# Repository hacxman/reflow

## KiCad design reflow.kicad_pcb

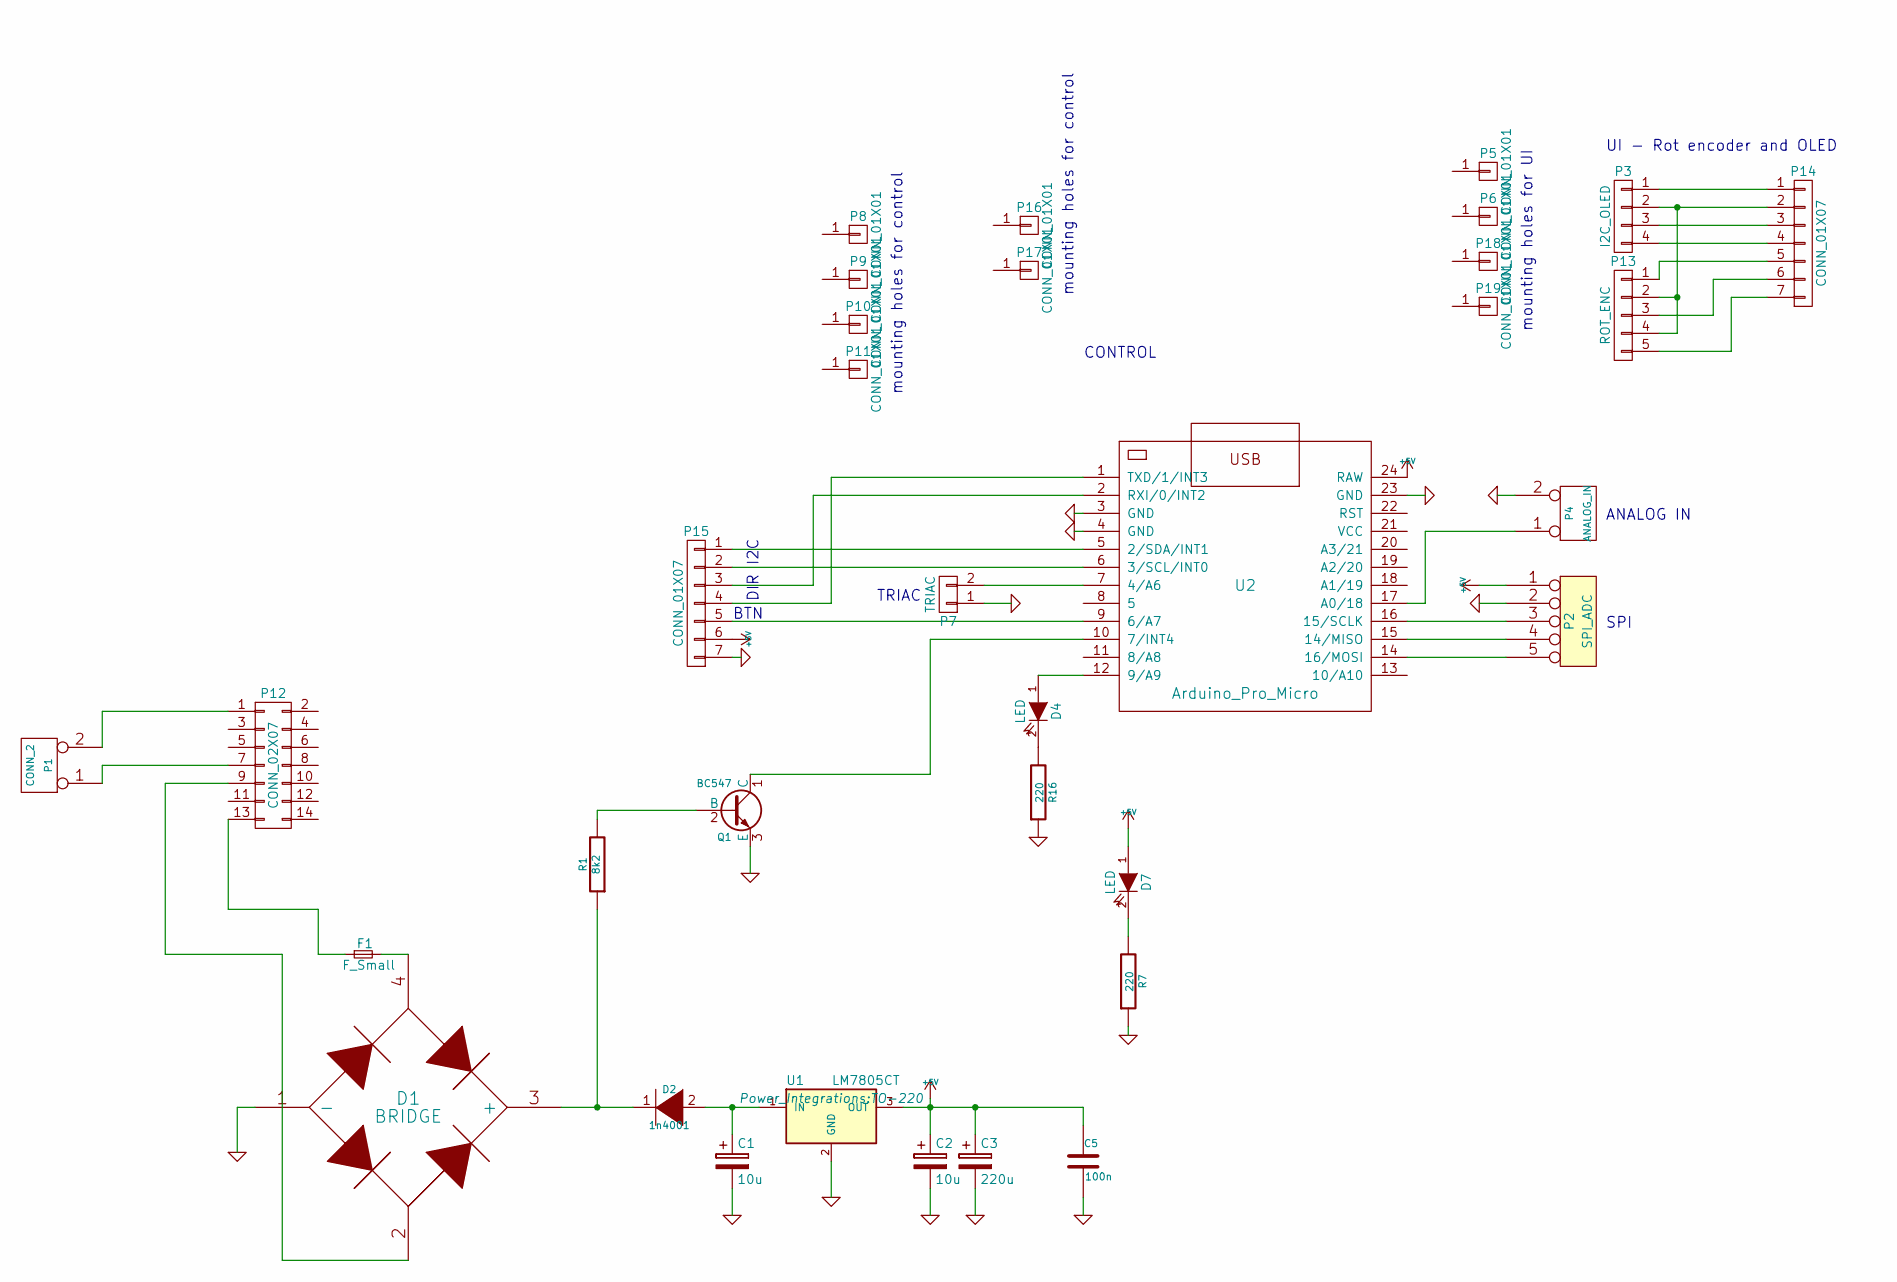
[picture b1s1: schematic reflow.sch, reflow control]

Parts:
C1, C2: 10u; C_Radial_D6.3_L11.2_P2.5
C3: 220u; C_Radial_D6.3_L11.2_P2.5
C5: 100n; C_Rect_L7_W2.5_P5
D1: BRIDGE; SDB107
D2: 1n4001; Diode_DO-35_SOD27_Horizontal_RM10
D4, D7: LED; LED-5MM
F1: F_Small; Fuseholder5x20_horiz_SemiClosed_Casing10x25mm
P1: CONN_2; TerminalBlock_Pheonix_MPT-2.54mm_2pol
P2: SPI_ADC; Pin_Header_Straight_1x05
P3: I2C_OLED; Pin_Header_Straight_1x04
P4: ANALOG_IN; Pin_Header_Straight_1x02
P5, P6, P8, P9, P10, P11, P16, P17, P18, P19: CONN_01X01; MountingHole_3mm
P7: TRIAC; Pin_Header_Straight_1x02
P12: CONN_02X07; Trafo_CHK-EI54-16VA_1xSec
P13: ROT_ENC; ROT_ENC_DIP-6_W15.24mm_LongPads
P14, P15: CONN_01X07; Pin_Header_Straight_1x07
Q1: BC547; TO-92_Molded_Wide_Oval
R1: 8k2; Resistor_Horizontal_RM10mm
R7, R16: 220; Resistor_Horizontal_RM10mm
U1: LM7805CT; TO-220
U2: Arduino_Pro_Micro; DIP-24_W15.24mm_LongPads

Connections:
+5V: C2.1, C3.1, C5.1, D7.1 (A), P2.1, P15.6, U1.3 (OUT), U2.24 (RAW)
GND: C1.2, C2.2, C3.2, C5.2, D1.1 (-), P2.2, P4.2 (PM), P7.1, P15.7, Q1.3 (E), R7.1, R16.1, U1.2 (GND), U2.3 (GND), U2.4 (GND), U2.23 (GND)
unnamed: C1.1, D2.2 (A), U1.1 (IN)
unnamed: D1.2, P12.9
unnamed: D1.3 (+), D2.1 (K), R1.1
unnamed: D1.4, F1.2
unnamed: D4.1 (A), U2.12 (9/A9)
unnamed: D4.2 (K), R16.2
unnamed: D7.2 (K), R7.2
unnamed: F1.1, P12.13
unnamed: P1.1, P12.7
unnamed: P1.2 (PM), P12.1
unnamed: P2.3, U2.16 (15/SCLK)
unnamed: P2.4, U2.15 (14/MISO)
unnamed: P2.5, U2.14 (16/MOSI)
unnamed: P4.1, U2.17 (A0/18)
unnamed: P7.2, U2.7 (4/A6)
unnamed: P13.1, P14.5
unnamed: P3.2, P13.2, P13.4, P14.2
unnamed: P13.3, P14.6
unnamed: P13.5, P14.7
unnamed: P3.1, P14.1
unnamed: P3.3, P14.3
unnamed: P3.4, P14.4
unnamed: P15.1, U2.5 (2/SDA/INT1)
unnamed: P15.2, U2.6 (3/SCL/INT0)
unnamed: P15.3, U2.2 (RXI/0/INT2)
unnamed: P15.4, U2.1 (TXD/1/INT3)
unnamed: P15.5, U2.9 (6/A7)
unnamed: Q1.1 (C), U2.10 (7/INT4)
unnamed: Q1.2 (B), R1.2

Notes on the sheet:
ANALOG IN
CONTROL
TRIAC
SPI
mounting holes for control
DIR
BTN
I2C
UI - Rot encoder and OLED
mounting holes for UI

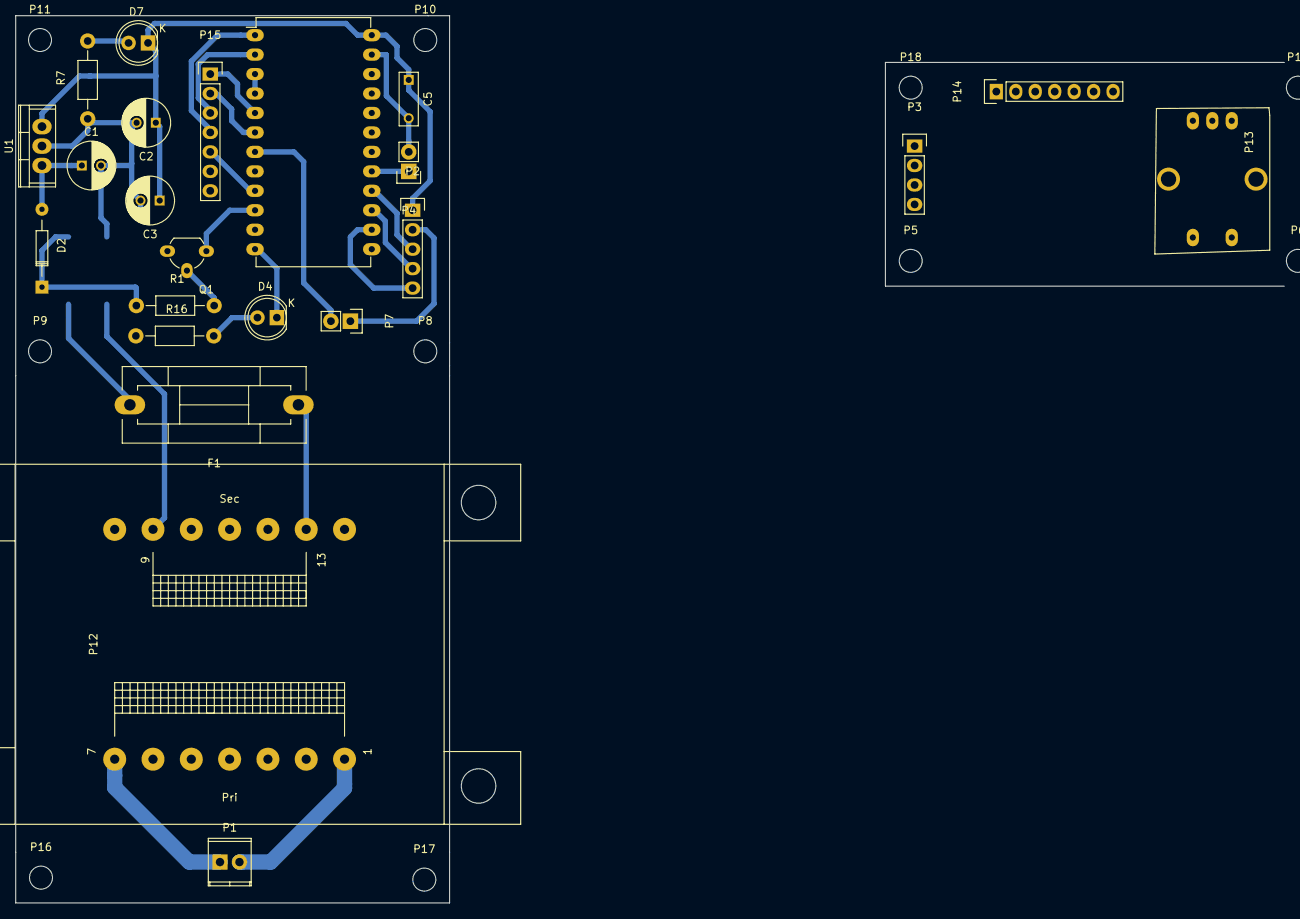
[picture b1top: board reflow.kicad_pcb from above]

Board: 2 copper layers, 165.6 x 115.8 mm, 34 parts (1 on the bottom side), 31 nets.

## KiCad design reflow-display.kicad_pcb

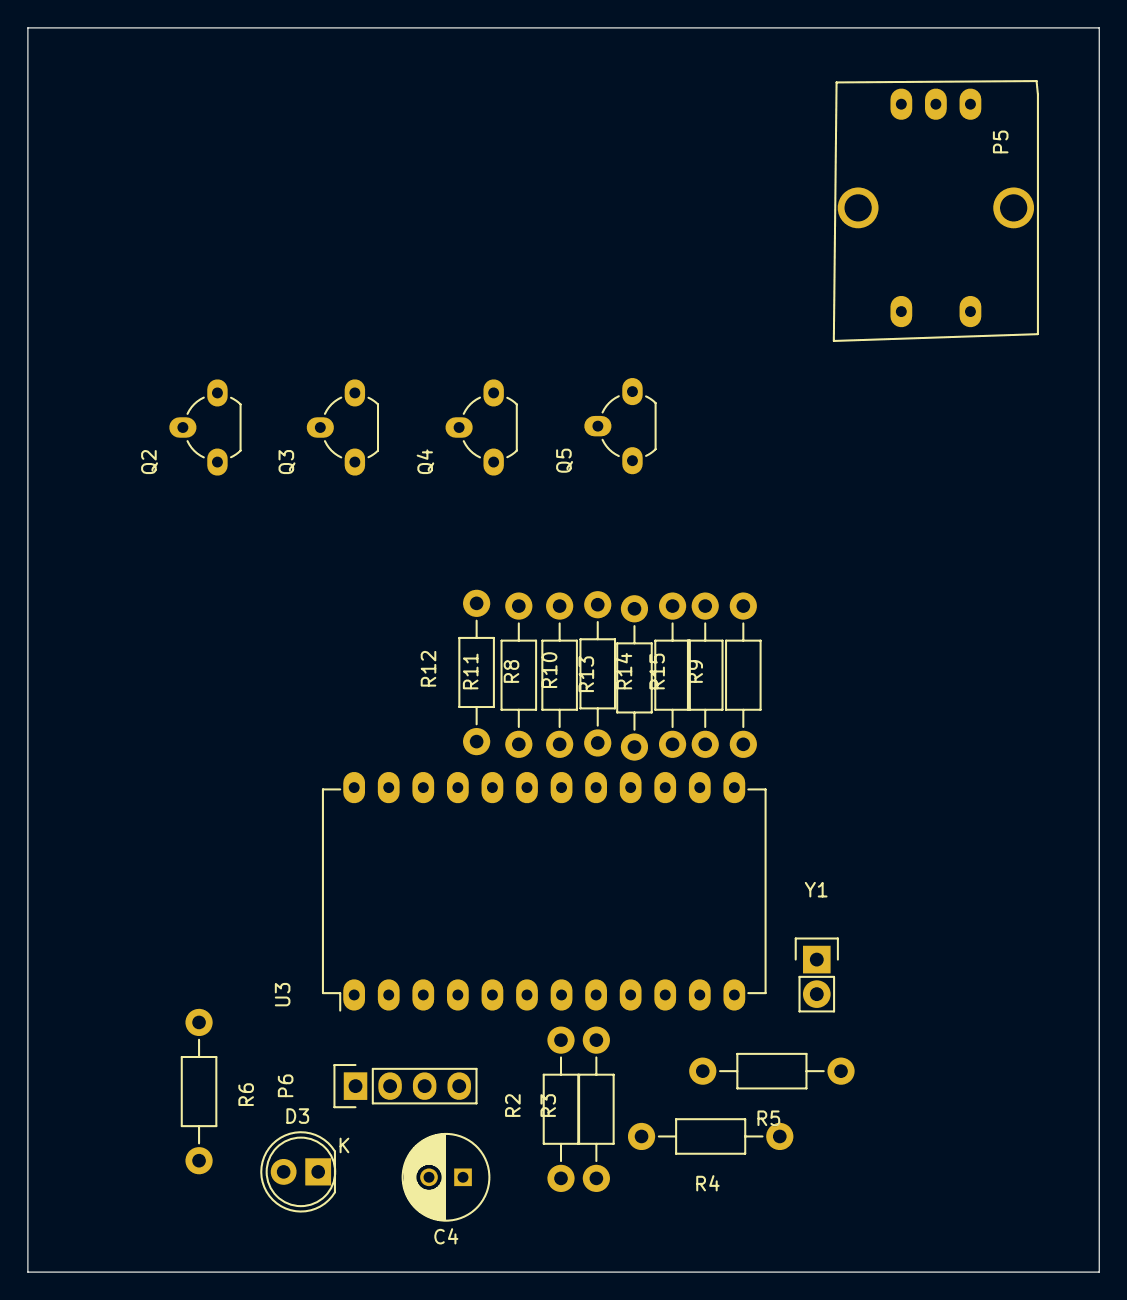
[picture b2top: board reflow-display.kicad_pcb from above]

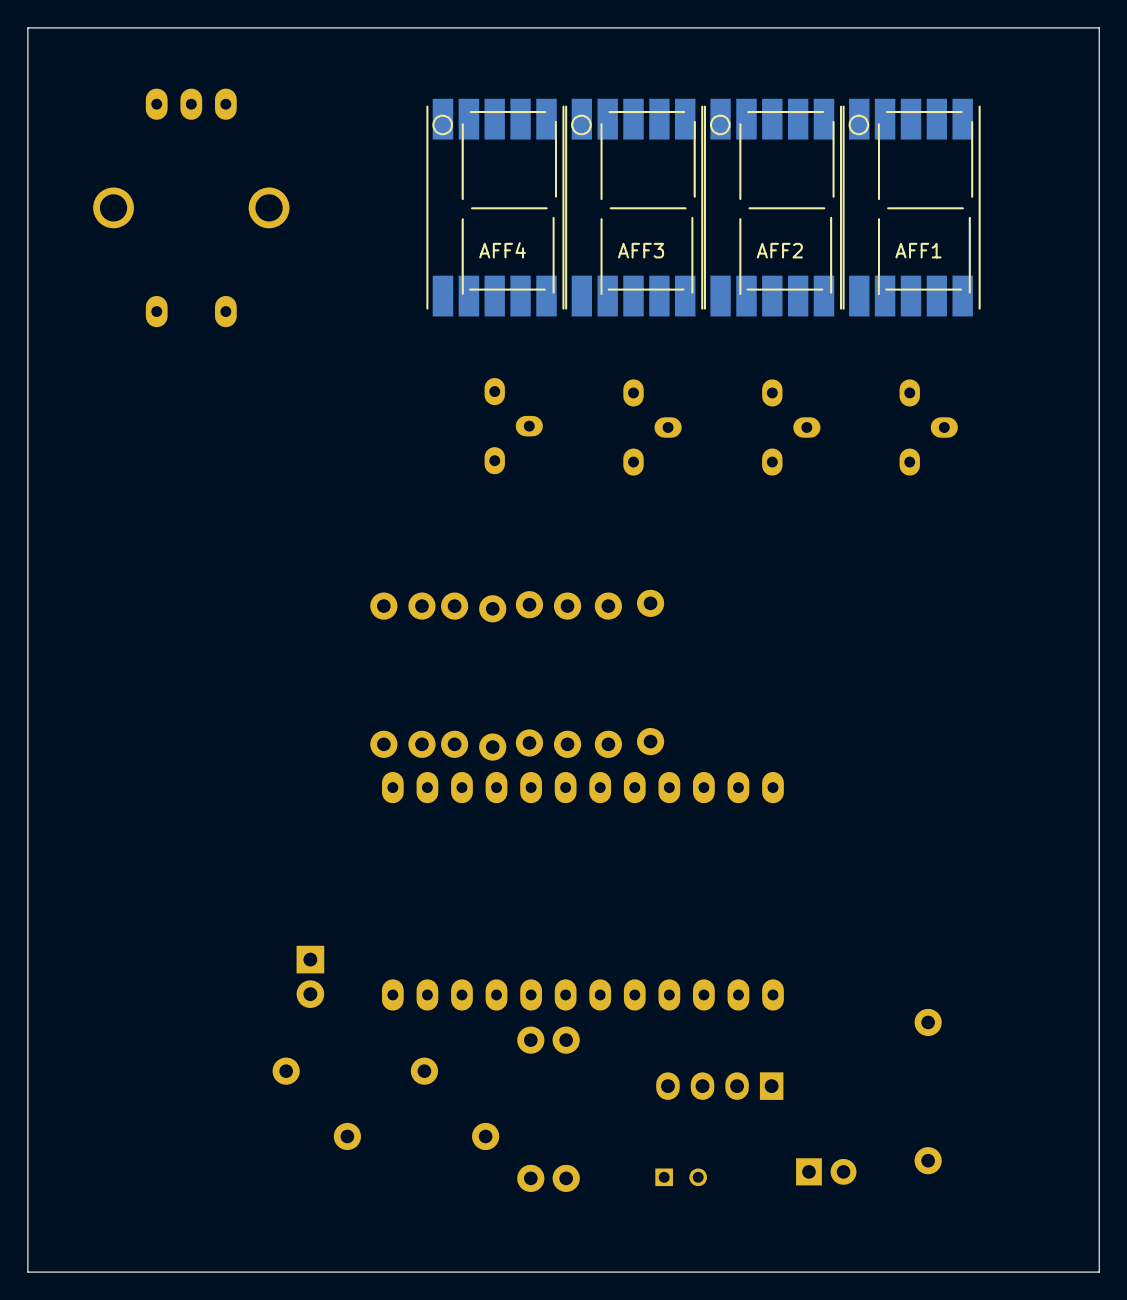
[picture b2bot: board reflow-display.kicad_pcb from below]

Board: 2 copper layers, 78.7 x 91.4 mm, 27 parts (4 on the bottom side), 38 nets, no tracks yet.

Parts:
AFF1, AFF2, AFF3, AFF4: 7SEGMENTS; 7SEGMENT-LED__HDSM531_HDSM533_SMD
C4: 220u; C_Radial_D6.3_L11.2_P2.5
D3: LED; LED-5MM
P5: CONN_01X05; ROT_ENC_DIP-6_W15.24mm_LongPads
P6: CONN_01X04; Pin_Header_Straight_1x04
Q2, Q3, Q4, Q5: BC547; TO-92_Molded_Wide_Oval
R2, R3, R4, R5, R8, R9, R10, R11, R12, R13, R14, R15: 1k; Resistor_Horizontal_RM10mm
R6: 220; Resistor_Horizontal_RM10mm
U3: Arduino_Pro_Micro; DIP-24_W15.24mm_LongPads
Y1: PIEZO; Pin_Header_Straight_1x02

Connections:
+5V: C4.1, D3.1, P6.4, U3.24
/SEG1: R12.1, U3.20
/SEG2: R13.1, U3.16
/SEG3: R14.1, U3.15
/SEG4: R15.1, U3.14
GND: C4.2, P5.2, P5.5, P6.3, R6.1, U3.3, U3.4, U3.23, Y1.1
unnamed: AFF1.1, AFF2.1, AFF3.1, AFF4.1, R4.1
unnamed: AFF1.2, AFF2.2, AFF3.2, AFF4.2, R5.1
unnamed: AFF1.3, AFF1.8, Q2.3
unnamed: AFF1.4, AFF2.4, AFF3.4, AFF4.4, R9.2
unnamed: AFF1.5, AFF2.5, AFF3.5, AFF4.5, R11.2
unnamed: AFF1.6, AFF2.6, AFF3.6, AFF4.6, R10.2
unnamed: AFF1.7, AFF2.7, AFF3.7, AFF4.7, R8.2
unnamed: AFF1.9, AFF2.9, AFF3.9, AFF4.9, R3.1
unnamed: AFF1.10, AFF2.10, AFF3.10, AFF4.10, R2.1
unnamed: AFF2.3, AFF2.8, Q3.3
unnamed: AFF3.3, AFF3.8, Q4.3
unnamed: AFF4.3, AFF4.8, Q5.3
unnamed: D3.2, R6.2
unnamed: P5.1, U3.5
unnamed: P5.3, U3.6
unnamed: P5.4, U3.10
unnamed: P6.1, U3.1
unnamed: P6.2, U3.2
unnamed: Q2.2, R12.2
unnamed: Q3.2, R13.2
unnamed: Q4.2, R14.2
unnamed: Q5.2, R15.2
unnamed: R2.2, U3.7
unnamed: R3.2, U3.8
unnamed: R4.2, U3.9
unnamed: R5.2, U3.11
unnamed: R8.1, U3.18
unnamed: R9.1, U3.13
unnamed: R10.1, U3.17
unnamed: R11.1, U3.19
unnamed: U3.12, Y1.2
VCC: Q2.1, Q3.1, Q4.1, Q5.1, U3.21

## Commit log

2016-10-16 first
2016-10-16 rotate control pcb
